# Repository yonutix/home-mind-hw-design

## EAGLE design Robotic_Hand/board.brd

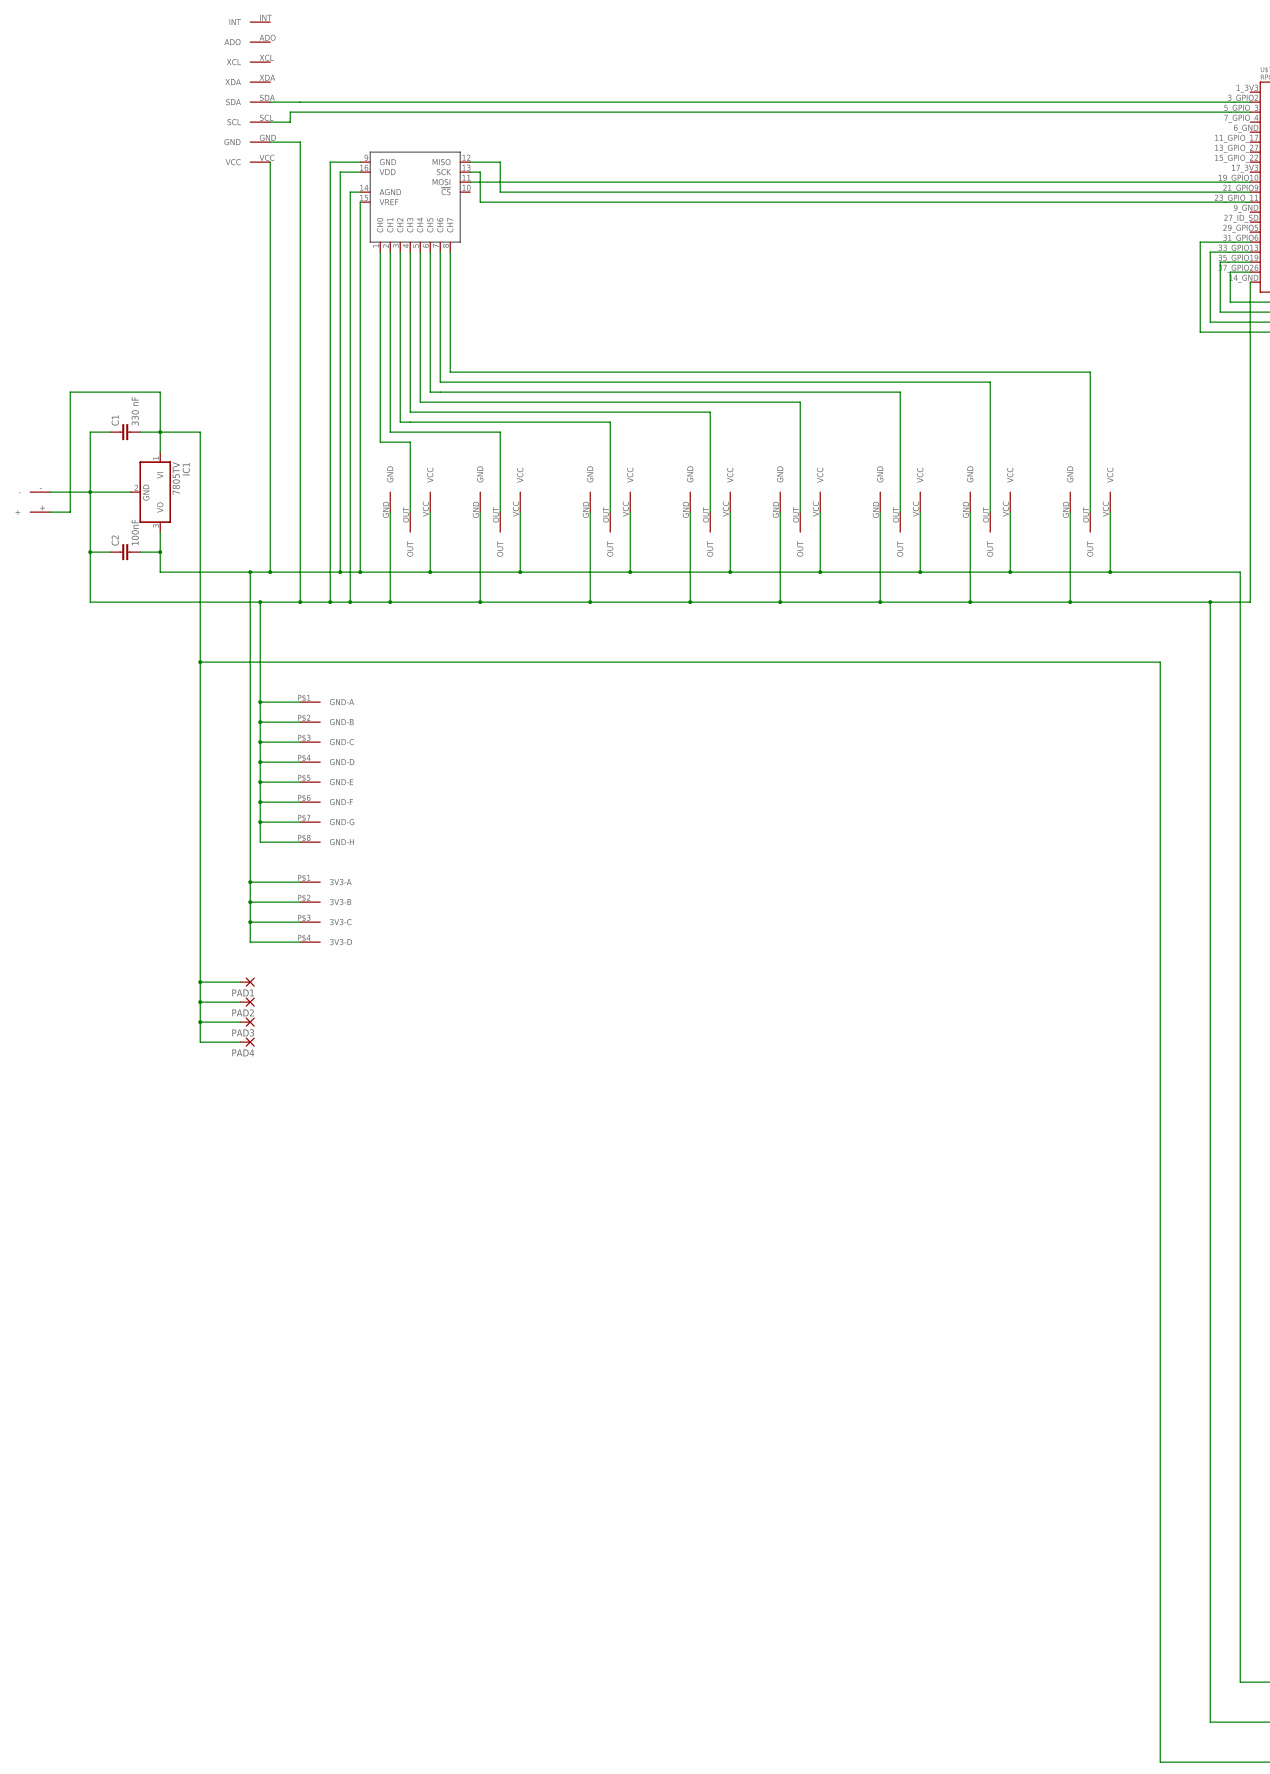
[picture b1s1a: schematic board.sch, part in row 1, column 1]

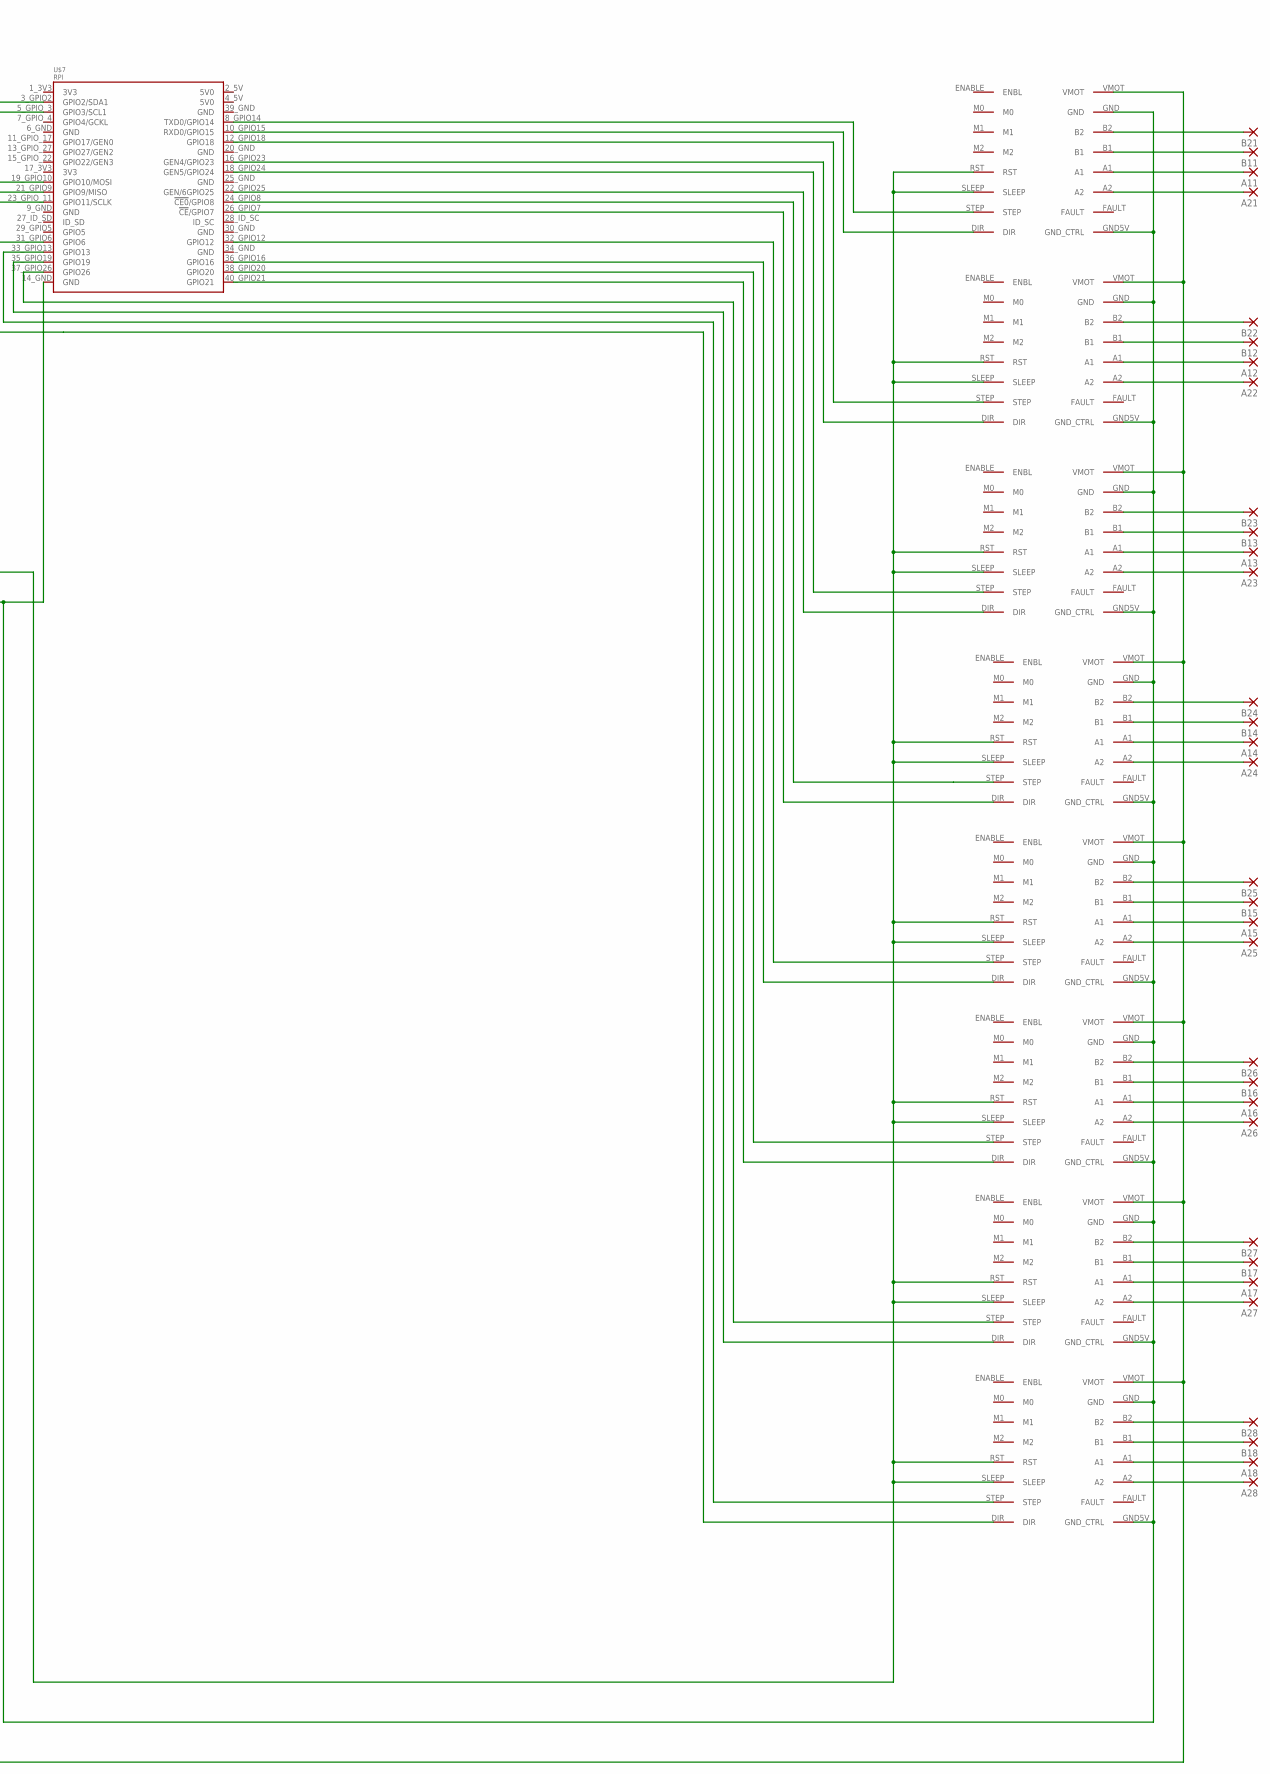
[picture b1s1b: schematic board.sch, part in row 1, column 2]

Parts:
A11, A12, A13, A14, A15, A16, A17, A18, A21, A22, A23, A24, A25, A26, A27, A28: 1,6/0,9
B11, B12, B13, B14, B15, B16, B17, B18, B21, B22, B23, B24, B25, B26, B27, B28: 1,6/0,9
C1: 330 nF; C2.5-2
C2: 100nF; C2.5-2
IC1: 7805TV; TO220V
PAD1, PAD2, PAD3, PAD4: 1,6/0,9
U$1: 12V_SRC
U$2, U$3, U$5, U$8, U$9, U$10, U$13, U$14: DISTANCE_SENSOR_ANALOG
U$4: MCP3008P; DIL16
U$6: MPU6050
U$7: RPI
U$11: 3V3-4; 3.3V-4
U$12: GND-8
U$15, U$16, U$17, U$18, U$19, U$20, U$21, U$22: DRV8825-SLOT

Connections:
GND@3: C1.1, C2.1, IC1.2 (GND), U$1.-, U$2.GND, U$3.GND, U$4.9 (GND), U$4.14 (AGND), U$5.GND, U$6.GND, U$7.14_GND (GND), U$8.GND, U$9.GND, U$10.GND, U$12.P$1 (GND-A), U$12.P$2 (GND-B), U$12.P$3 (GND-C), U$12.P$4 (GND-D), U$12.P$5 (GND-E), U$12.P$6 (GND-F), U$12.P$7 (GND-G), U$12.P$8 (GND-H), U$13.GND, U$14.GND, U$15.GND, U$15.GND5V (GND_CTRL), U$16.GND, U$16.GND5V (GND_CTRL), U$17.GND, U$17.GND5V (GND_CTRL), U$18.GND, U$18.GND5V (GND_CTRL), U$19.GND, U$19.GND5V (GND_CTRL), U$20.GND, U$20.GND5V (GND_CTRL), U$21.GND, U$21.GND5V (GND_CTRL), U$22.GND, U$22.GND5V (GND_CTRL)
unnamed: U$4.1 (CH0), U$9.OUT
unnamed: U$4.2 (CH1), U$10.OUT
unnamed: U$4.3 (CH2), U$14.OUT
unnamed: U$4.4 (CH3), U$13.OUT
unnamed: U$2.OUT, U$4.5 (CH4)
unnamed: U$3.OUT, U$4.6 (CH5)
unnamed: U$4.7 (CH6), U$5.OUT
unnamed: U$6.SDA, U$7.3_GPIO2 (GPIO2/SDA1)
unnamed: U$4.8 (CH7), U$8.OUT
unnamed: U$6.SCL, U$7.5_GPIO_3 (GPIO3/SCL1)
unnamed: C2.2, IC1.3 (VO), U$2.VCC, U$3.VCC, U$4.15 (VREF), U$4.16 (VDD), U$5.VCC, U$6.VCC, U$8.VCC, U$9.VCC, U$10.VCC, U$11.P$1 (3V3-A), U$11.P$2 (3V3-B), U$11.P$3 (3V3-C), U$11.P$4 (3V3-D), U$13.VCC, U$14.VCC, U$15.RST, U$15.SLEEP, U$16.RST, U$16.SLEEP, U$17.RST, U$17.SLEEP, U$18.RST, U$18.SLEEP, U$19.RST, U$19.SLEEP, U$20.RST, U$20.SLEEP, U$21.RST, U$21.SLEEP, U$22.RST, U$22.SLEEP
unnamed: C1.2, IC1.1 (VI), PAD1.1, PAD2.1, PAD3.1, PAD4.1, U$1.+, U$15.VMOT, U$16.VMOT, U$17.VMOT, U$18.VMOT, U$19.VMOT, U$20.VMOT, U$21.VMOT, U$22.VMOT
unnamed: U$7.8_GPIO14 (TXD0/GPIO14), U$15.STEP
unnamed: U$4.11 (MOSI), U$7.19_GPIO10 (GPIO10/MOSI)
unnamed: U$4.12 (MISO), U$7.21_GPIO9 (GPIO9/MISO)
unnamed: U$4.13 (SCK), U$7.23_GPIO_11 (GPIO11/SCLK)
unnamed: U$7.10_GPIO15 (RXD0/GPIO15), U$15.DIR
unnamed: U$7.12_GPIO18 (GPIO18), U$16.STEP
unnamed: U$7.16_GPIO23 (GEN4/GPIO23), U$16.DIR
unnamed: U$7.18_GPIO24 (GEN5/GPIO24), U$17.STEP
unnamed: U$7.22_GPIO25 (GEN/6GPIO25), U$17.DIR
unnamed: U$7.24_GPIO8 (!CE0!/GPIO8), U$18.STEP
unnamed: U$7.26_GPIO7 (!CE!/GPIO7), U$18.DIR
unnamed: B21.1, U$15.B2
unnamed: B11.1, U$15.B1
unnamed: A11.1, U$15.A1
unnamed: A21.1, U$15.A2
unnamed: B22.1, U$16.B2
unnamed: B12.1, U$16.B1
unnamed: B25.1, U$19.B2
unnamed: A12.1, U$16.A1
unnamed: A22.1, U$16.A2
unnamed: B23.1, U$17.B2
unnamed: B13.1, U$17.B1
unnamed: A13.1, U$17.A1
unnamed: A23.1, U$17.A2
unnamed: B24.1, U$18.B2
unnamed: B14.1, U$18.B1
unnamed: A14.1, U$18.A1
unnamed: A24.1, U$18.A2
unnamed: B15.1, U$19.B1
unnamed: A15.1, U$19.A1
unnamed: A25.1, U$19.A2
unnamed: B26.1, U$20.B2
unnamed: B16.1, U$20.B1
unnamed: A16.1, U$20.A1
unnamed: A26.1, U$20.A2
unnamed: B27.1, U$21.B2
unnamed: B17.1, U$21.B1
unnamed: A17.1, U$21.A1
unnamed: A27.1, U$21.A2
unnamed: B28.1, U$22.B2
unnamed: B18.1, U$22.B1
unnamed: A18.1, U$22.A1
unnamed: A28.1, U$22.A2
unnamed: U$7.32_GPIO12 (GPIO12), U$19.STEP
unnamed: U$7.36_GPIO16 (GPIO16), U$19.DIR
unnamed: U$7.38_GPIO20 (GPIO20), U$20.STEP
unnamed: U$7.40_GPIO21 (GPIO21), U$20.DIR
unnamed: U$7.37_GPIO26 (GPIO26), U$21.STEP
unnamed: U$7.35_GPIO19 (GPIO19), U$21.DIR
unnamed: U$7.33_GPIO13 (GPIO13), U$22.STEP
unnamed: U$7.31_GPIO6 (GPIO6), U$22.DIR

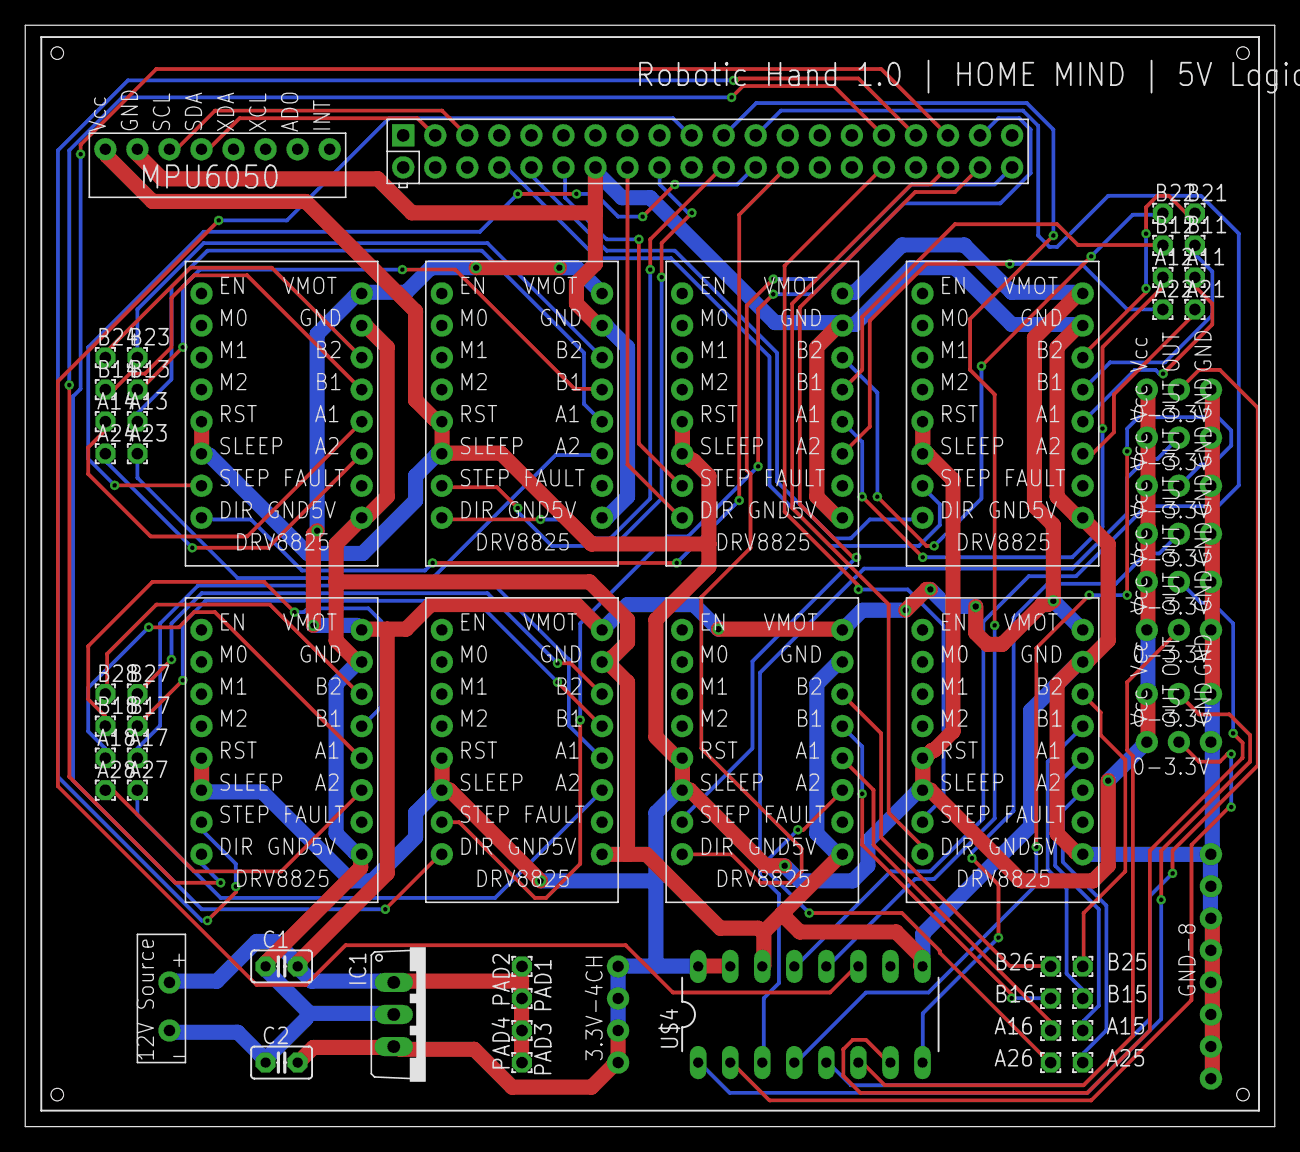
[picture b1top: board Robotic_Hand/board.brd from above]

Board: 2 copper layers, 99.0 x 87.3 mm, 61 parts (0 on the bottom side), 64 nets.

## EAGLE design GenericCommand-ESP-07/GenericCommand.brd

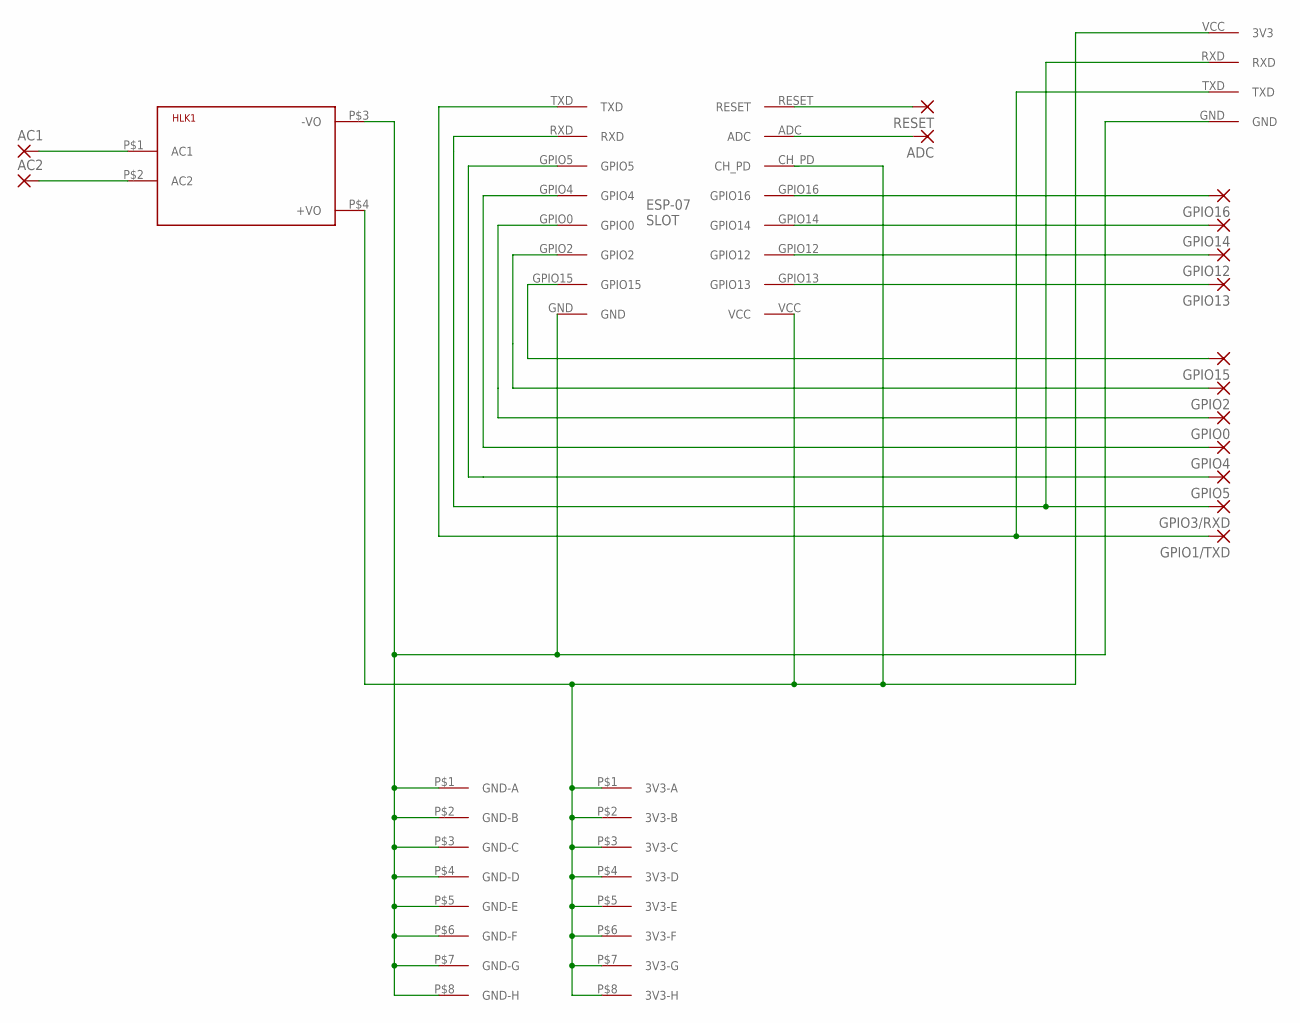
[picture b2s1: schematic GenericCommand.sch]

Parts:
AC1, AC2: 3,81/1,4
ADC: 1,6/0,9
GPIO0, GPIO1/TXD, GPIO2, GPIO3/RXD, GPIO4, GPIO5, GPIO12, GPIO13, GPIO14, GPIO15, GPIO16: 1,6/0,9
HLK1: HLK-PM013W; HLK-PM01
RESET: 1,6/0,9
U$1: ESP-07
U$2: CP-2102-CONN
U$3: 3V3-8; 3.3V-8
U$4: GND-8

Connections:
unnamed: GPIO15.1, U$1.GPIO15
unnamed: HLK1.P$3 (-VO), U$1.GND, U$2.GND, U$4.P$1 (GND-A), U$4.P$2 (GND-B), U$4.P$3 (GND-C), U$4.P$4 (GND-D), U$4.P$5 (GND-E), U$4.P$6 (GND-F), U$4.P$7 (GND-G), U$4.P$8 (GND-H)
unnamed: GPIO2.1, U$1.GPIO2
unnamed: GPIO0.1, U$1.GPIO0
unnamed: GPIO16.1, U$1.GPIO16
unnamed: GPIO14.1, U$1.GPIO14
unnamed: GPIO12.1, U$1.GPIO12
unnamed: GPIO13.1, U$1.GPIO13
unnamed: GPIO4.1, U$1.GPIO4
unnamed: HLK1.P$4 (+VO), U$1.CH_PD, U$1.VCC, U$2.VCC (3V3), U$3.P$1 (3V3-A), U$3.P$2 (3V3-B), U$3.P$3 (3V3-C), U$3.P$4 (3V3-D), U$3.P$5 (3V3-E), U$3.P$6 (3V3-F), U$3.P$7 (3V3-G), U$3.P$8 (3V3-H)
unnamed: GPIO5.1, U$1.GPIO5
unnamed: GPIO3/RXD.1, U$1.RXD, U$2.RXD
unnamed: GPIO1/TXD.1, U$1.TXD, U$2.TXD
unnamed: ADC.1, U$1.ADC
unnamed: RESET.1, U$1.RESET
unnamed: AC2.1, HLK1.P$2 (AC2)
unnamed: AC1.1, HLK1.P$1 (AC1)

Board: 2 copper layers, 20 parts (0 on the bottom side), 17 nets, no tracks yet.

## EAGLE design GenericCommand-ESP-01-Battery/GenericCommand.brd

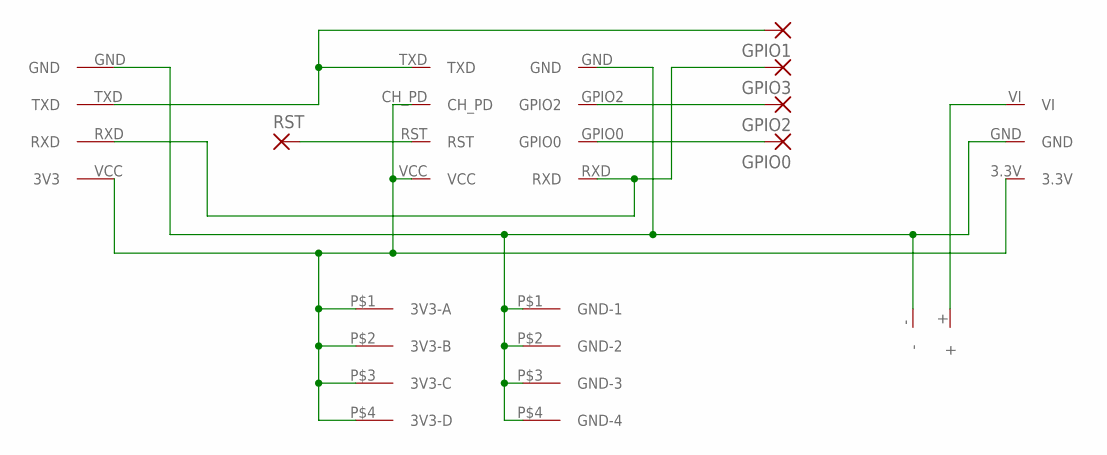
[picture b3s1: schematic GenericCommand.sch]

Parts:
GPIO0, GPIO1, GPIO2, GPIO3: 1,6/0,9
RST: 1,6/0,9
U$1: LOW_POWER
U$2: 3.3V-REG-SLOT
U$3: ESP-01-SLOT
U$4: CP-2102-CONN
U$5: 3V3-4; 3.3V-4
U$6: GND-4

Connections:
unnamed: U$2.3.3V, U$3.CH_PD, U$3.VCC, U$4.VCC (3V3), U$5.P$1 (3V3-A), U$5.P$2 (3V3-B), U$5.P$3 (3V3-C), U$5.P$4 (3V3-D)
unnamed: U$1.-, U$2.GND, U$3.GND, U$4.GND, U$6.P$1 (GND-1), U$6.P$2 (GND-2), U$6.P$3 (GND-3), U$6.P$4 (GND-4)
unnamed: U$1.+, U$2.VI
unnamed: GPIO0.1, U$3.GPIO0
unnamed: GPIO2.1, U$3.GPIO2
unnamed: RST.1, U$3.RST
unnamed: GPIO3.1, U$3.RXD, U$4.RXD
unnamed: GPIO1.1, U$3.TXD, U$4.TXD

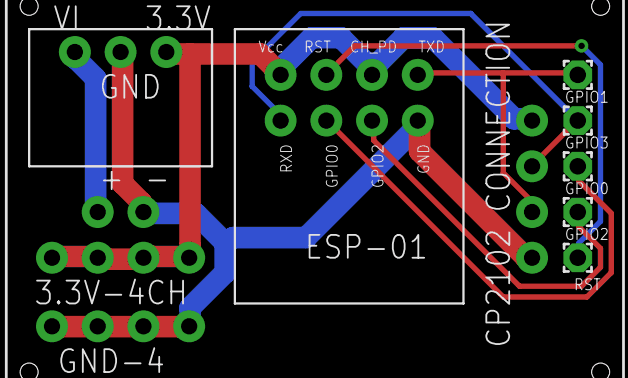
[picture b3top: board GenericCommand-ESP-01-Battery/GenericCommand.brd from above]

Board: 2 copper layers, 11 parts (0 on the bottom side), 8 nets.

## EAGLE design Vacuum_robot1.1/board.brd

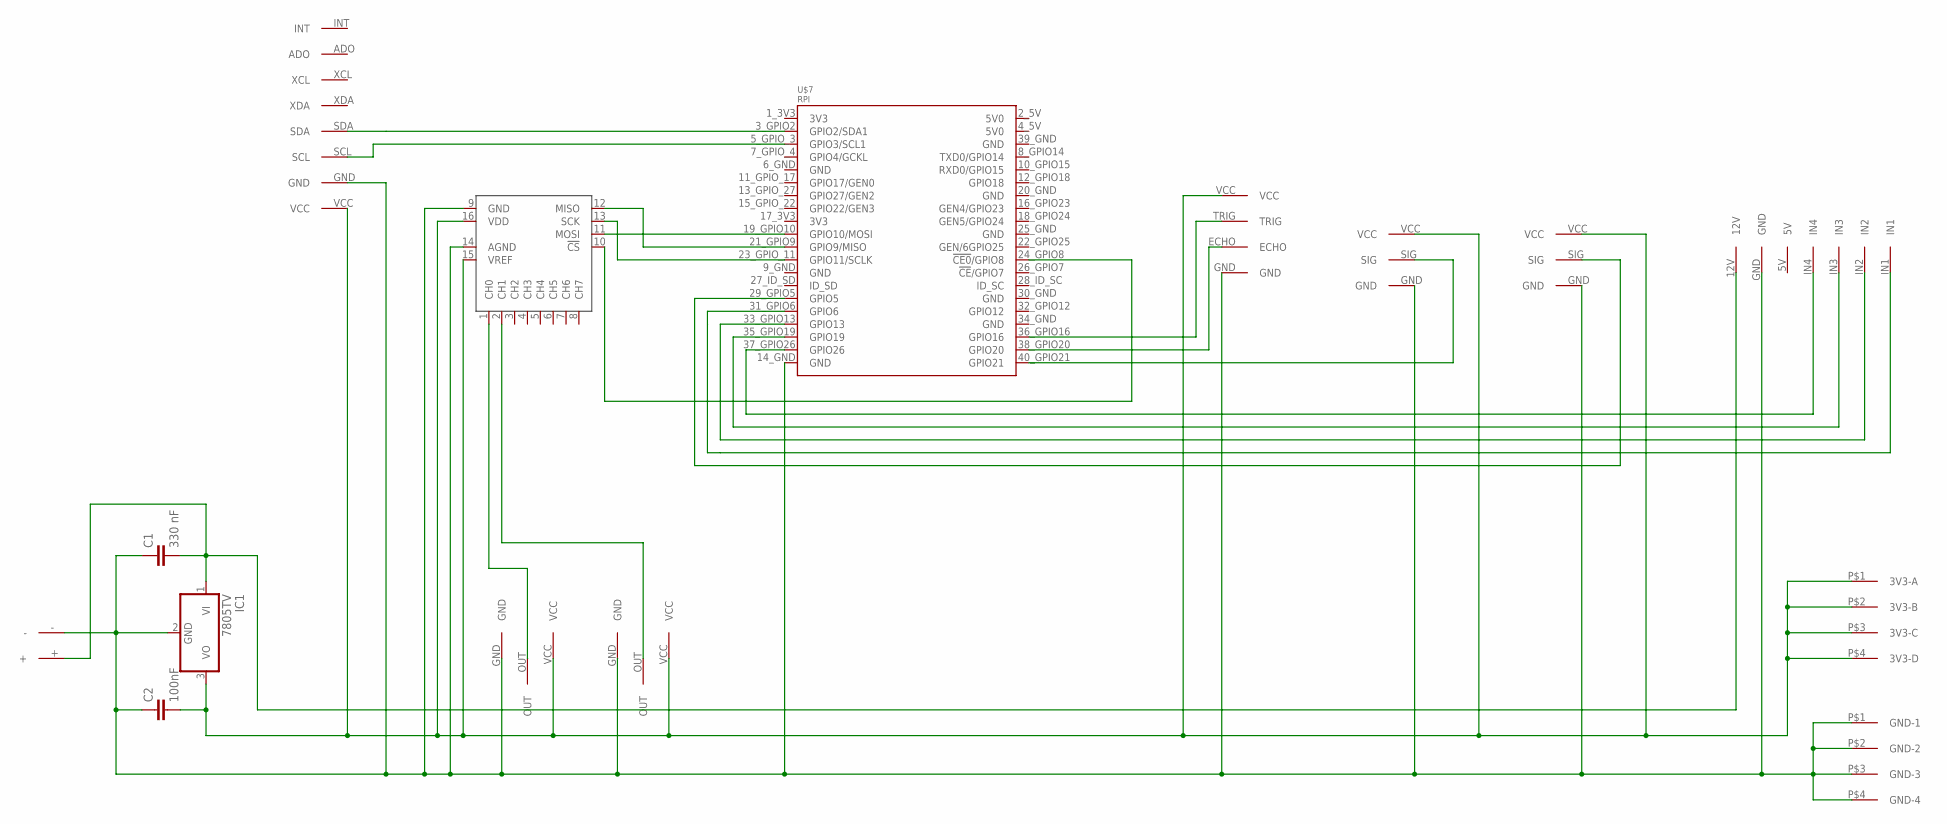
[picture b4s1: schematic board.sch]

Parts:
C1: 330 nF; C2.5-2
C2: 100nF; C2.5-2
IC1: 7805TV; TO220V
U$1: 12V_SRC
U$2, U$3: DC_REL
U$4: MCP3008P; DIL16
U$5: L298N-CONN
U$6: MPU6050
U$7: RPI
U$8: HC-SR04
U$9, U$10: DISTANCE_SENSOR_ANALOG
U$11: 3V3-4; 3.3V-4
U$12: GND-4

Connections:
GND@3: C1.1, C2.1, IC1.2 (GND), U$1.-, U$2.GND, U$3.GND, U$4.9 (GND), U$4.14 (AGND), U$5.GND, U$6.GND, U$7.14_GND (GND), U$8.GND, U$9.GND, U$10.GND, U$12.P$1 (GND-1), U$12.P$2 (GND-2), U$12.P$3 (GND-3), U$12.P$4 (GND-4)
unnamed: U$4.1 (CH0), U$9.OUT
unnamed: U$4.2 (CH1), U$10.OUT
unnamed: C1.2, IC1.1 (VI), U$1.+, U$5.12V
unnamed: U$6.SDA, U$7.3_GPIO2 (GPIO2/SDA1)
unnamed: U$6.SCL, U$7.5_GPIO_3 (GPIO3/SCL1)
unnamed: U$5.IN4, U$7.37_GPIO26 (GPIO26)
unnamed: U$4.11 (MOSI), U$7.19_GPIO10 (GPIO10/MOSI)
unnamed: U$4.12 (MISO), U$7.21_GPIO9 (GPIO9/MISO)
unnamed: U$4.13 (SCK), U$7.23_GPIO_11 (GPIO11/SCLK)
unnamed: U$4.10 (!CS), U$7.24_GPIO8 (!CE0!/GPIO8)
unnamed: U$5.IN3, U$7.35_GPIO19 (GPIO19)
unnamed: U$5.IN2, U$7.33_GPIO13 (GPIO13)
unnamed: U$5.IN1, U$7.31_GPIO6 (GPIO6)
unnamed: U$3.SIG, U$7.29_GPIO5 (GPIO5)
unnamed: U$2.SIG, U$7.40_GPIO21 (GPIO21)
unnamed: U$7.38_GPIO20 (GPIO20), U$8.ECHO
unnamed: U$7.36_GPIO16 (GPIO16), U$8.TRIG
unnamed: C2.2, IC1.3 (VO), U$2.VCC, U$3.VCC, U$4.15 (VREF), U$4.16 (VDD), U$6.VCC, U$8.VCC, U$9.VCC, U$10.VCC, U$11.P$1 (3V3-A), U$11.P$2 (3V3-B), U$11.P$3 (3V3-C), U$11.P$4 (3V3-D)

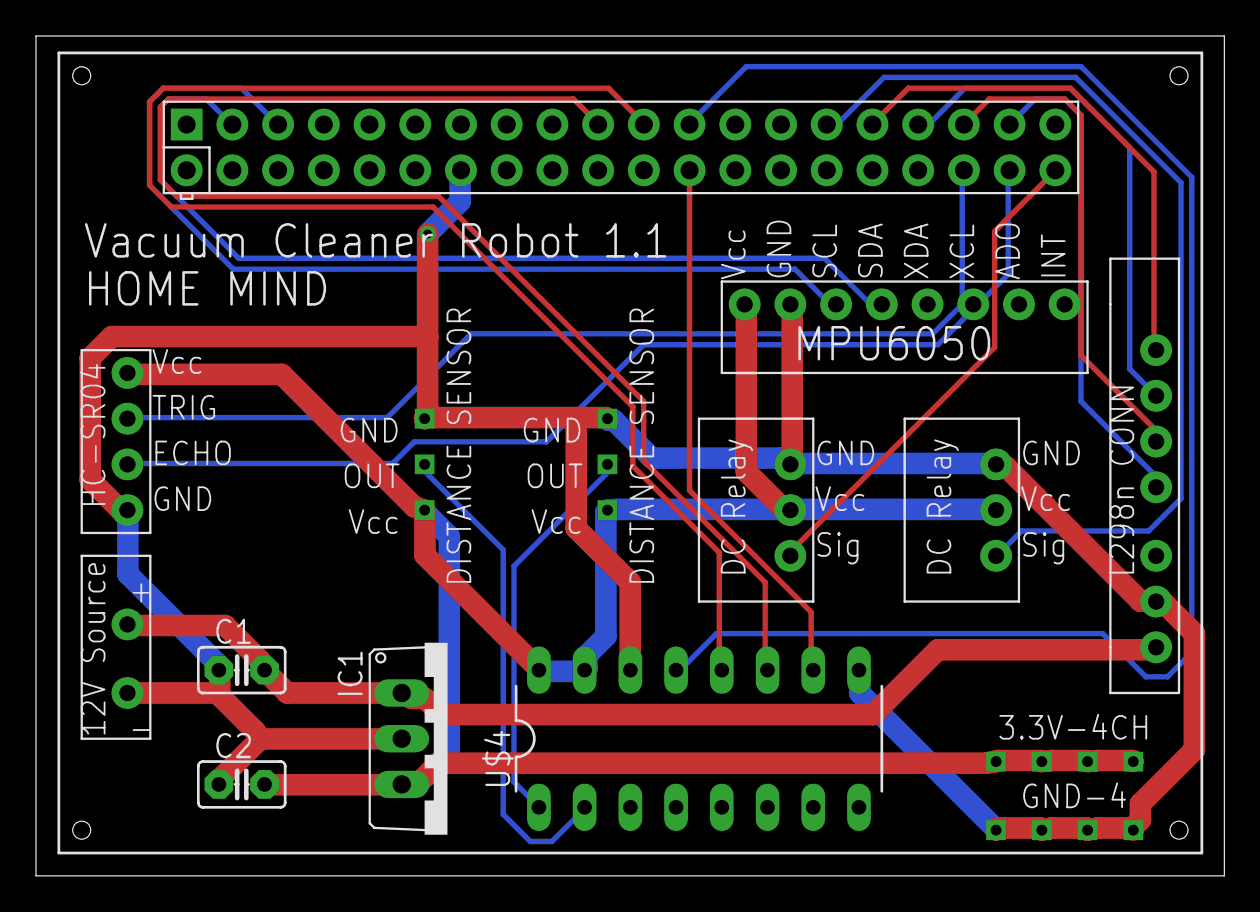
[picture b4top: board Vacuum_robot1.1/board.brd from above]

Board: 2 copper layers, 66.0 x 46.7 mm, 15 parts (0 on the bottom side), 19 nets.

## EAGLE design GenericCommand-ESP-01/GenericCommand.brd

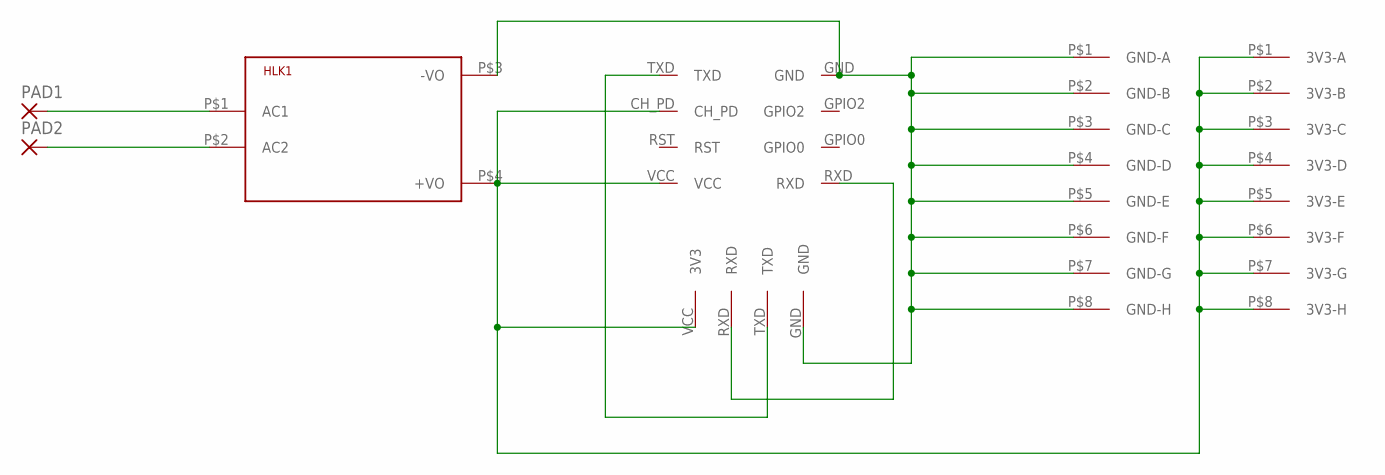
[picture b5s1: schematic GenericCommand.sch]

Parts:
HLK1: HLK-PM013W; HLK-PM01
PAD1, PAD2: 3,81/1,4
U$1: ESP-01-SLOT
U$2: CP-2102-CONN
U$3: 3V3-8; 3.3V-8
U$4: GND-8

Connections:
unnamed: HLK1.P$4 (+VO), U$1.CH_PD, U$1.VCC, U$2.VCC (3V3), U$3.P$1 (3V3-A), U$3.P$2 (3V3-B), U$3.P$3 (3V3-C), U$3.P$4 (3V3-D), U$3.P$5 (3V3-E), U$3.P$6 (3V3-F), U$3.P$7 (3V3-G), U$3.P$8 (3V3-H)
unnamed: HLK1.P$1 (AC1), PAD1.1
unnamed: HLK1.P$3 (-VO), U$1.GND, U$2.GND, U$4.P$1 (GND-A), U$4.P$2 (GND-B), U$4.P$3 (GND-C), U$4.P$4 (GND-D), U$4.P$5 (GND-E), U$4.P$6 (GND-F), U$4.P$7 (GND-G), U$4.P$8 (GND-H)
unnamed: U$1.RXD, U$2.RXD
unnamed: U$1.TXD, U$2.TXD
unnamed: HLK1.P$2 (AC2), PAD2.1

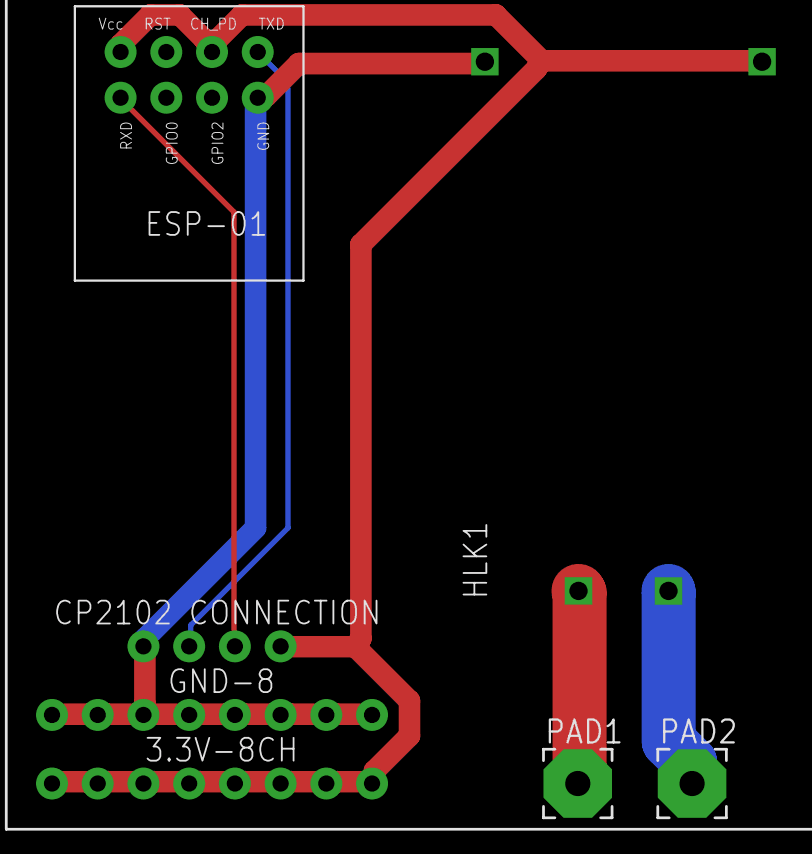
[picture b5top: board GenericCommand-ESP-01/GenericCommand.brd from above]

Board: 2 copper layers, 7 parts (0 on the bottom side), 6 nets.

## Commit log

2019-03-30 Add initial version
